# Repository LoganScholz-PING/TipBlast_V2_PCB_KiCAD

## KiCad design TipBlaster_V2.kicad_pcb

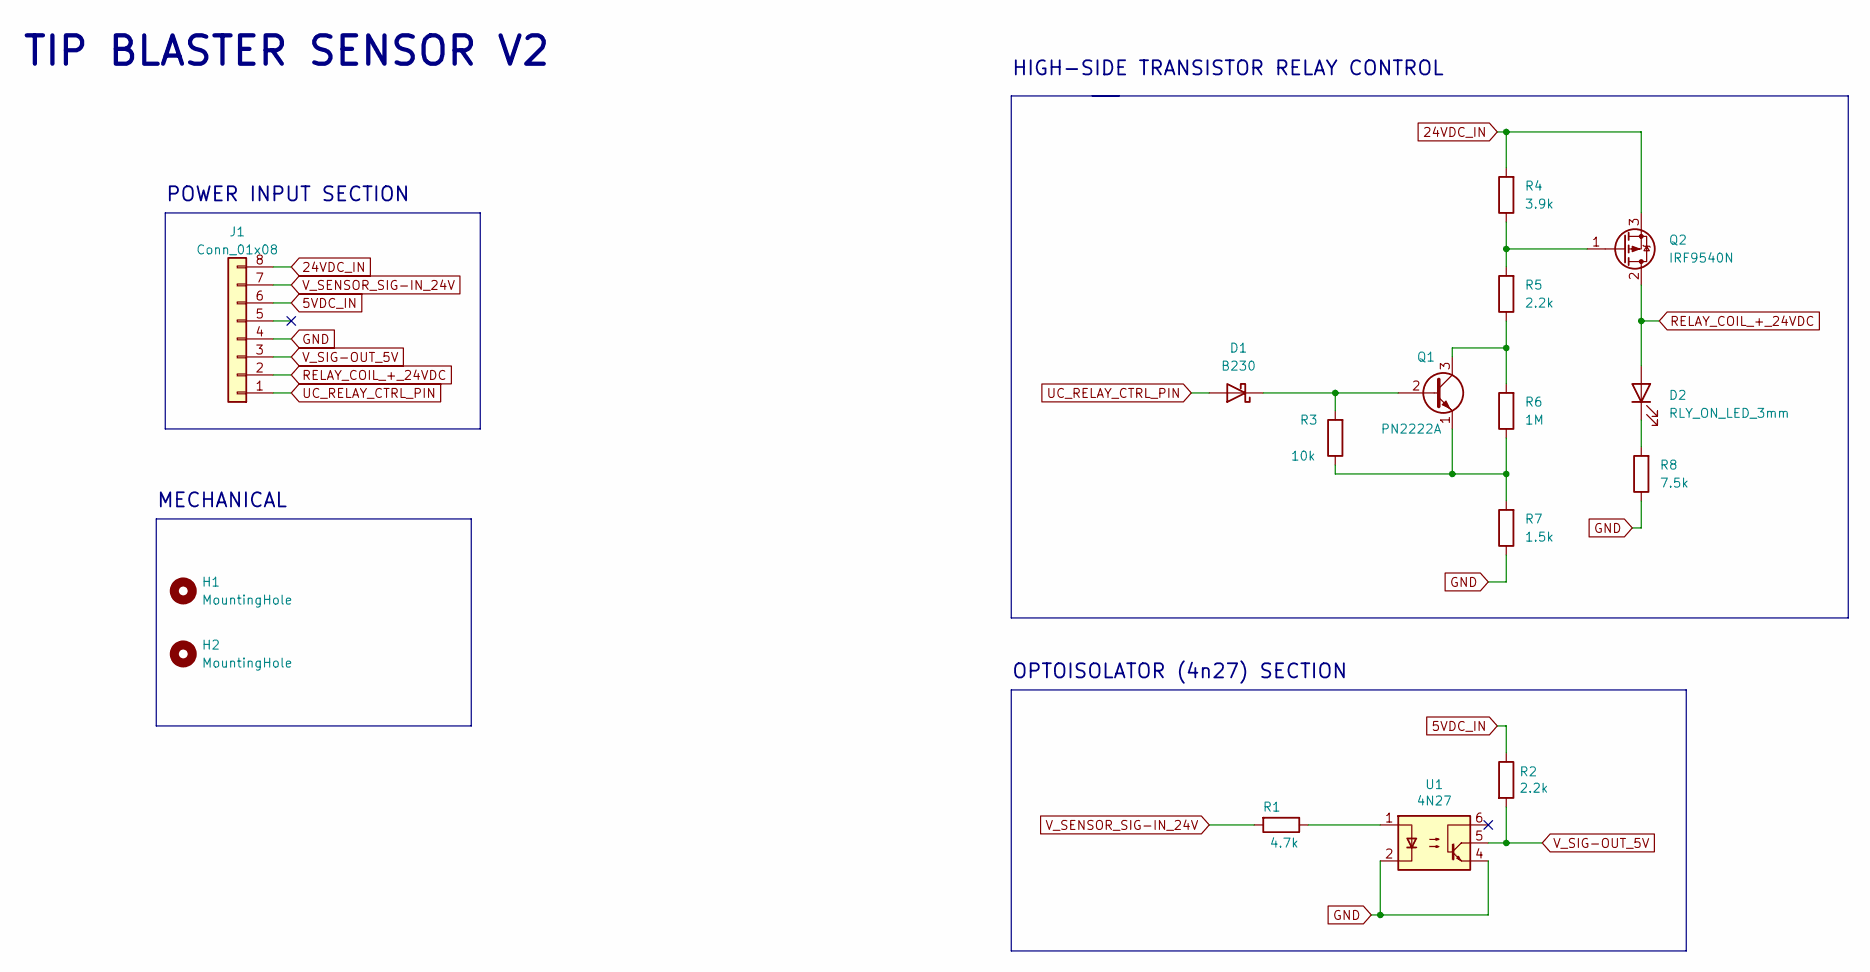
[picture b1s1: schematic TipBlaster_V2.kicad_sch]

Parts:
D1: B230; D_5W_P12.70mm_Horizontal
D2: RLY_ON_LED_3mm; LED_D3.0mm
H1, H2: MountingHole; MountingHole_3.5mm
J1: Conn_01x08; PinHeader_1x08_P2.54mm_Vertical
Q1: PN2222A; TO-18-3
Q2: IRF9540N; TO-220-3_Vertical
R1: 4.7k; R_Axial_DIN0207_L6.3mm_D2.5mm_P15.24mm_Horizontal
R2, R5: 2.2k; R_Axial_DIN0207_L6.3mm_D2.5mm_P15.24mm_Horizontal
R3: 10k; R_Axial_DIN0207_L6.3mm_D2.5mm_P15.24mm_Horizontal
R4: 3.9k; R_Axial_DIN0207_L6.3mm_D2.5mm_P15.24mm_Horizontal
R6: 1M; R_Axial_DIN0207_L6.3mm_D2.5mm_P15.24mm_Horizontal
R7: 1.5k; R_Axial_DIN0207_L6.3mm_D2.5mm_P15.24mm_Horizontal
R8: 7.5k; R_Axial_DIN0207_L6.3mm_D2.5mm_P15.24mm_Horizontal
U1: 4N27; DIP-6_W7.62mm

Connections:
5VDC_IN: J1.6, R2.1
24VDC_IN: J1.8, Q2.3 (S), R4.2
GND: J1.4, R7.1, R8.1, U1.2, U1.4
unnamed: D2.1 (K), R8.2
unnamed: Q1.1 (E), R3.1, R6.1, R7.2
unnamed: D1.1 (K), Q1.2 (B), R3.2
unnamed: Q1.3 (C), R5.1, R6.2
unnamed: Q2.1 (G), R4.1, R5.2
unnamed: R1.1, U1.1
RELAY_COIL_+_24VDC: D2.2 (A), J1.2, Q2.2 (D)
UC_RELAY_CTRL_PIN: D1.2 (A), J1.1
V_SENSOR_SIG-IN_24V: J1.7, R1.2
V_SIG-OUT_5V: J1.3, R2.2, U1.5

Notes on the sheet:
POWER INPUT SECTION
HIGH-SIDE TRANSISTOR RELAY CONTROL
TIP BLASTER SENSOR V2
MECHANICAL
OPTOISOLATOR (4n27) SECTION

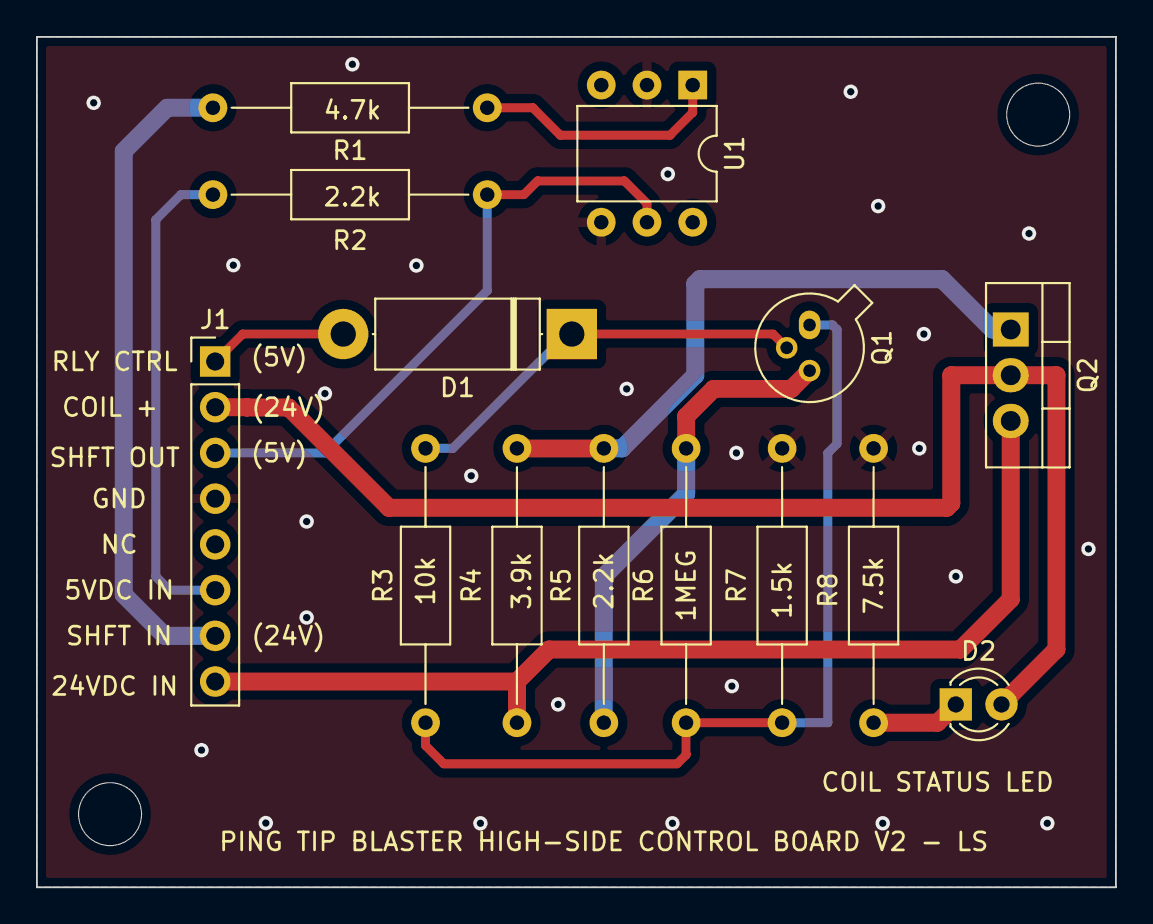
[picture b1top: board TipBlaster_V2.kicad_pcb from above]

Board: 2 copper layers, 59.9 x 47.2 mm, 16 parts (0 on the bottom side), 13 nets.

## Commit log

2022-11-04 initial commit
    ready for JLCPCB
